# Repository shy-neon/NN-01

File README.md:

# NN-01
IR bridge based on attiny-85
</br>
</br>

</br>

## Description 
Imagine having different IR devices (e.g. a TV and an Home theatre hoked to it) each of them controlled by its own remote. This device allows you to control both of them with the same remote.
It can be field programmed (according to the flow diagram below) to emit a specific IR commad whenever a source IR command is recived, this can be useful to automate some scenarios (like turnig on the home theatre whenever the tv is turned on or controlling the volume from the TV remote).
This is expecially usefull when a generic universal remote cannot be used (modern smart TVs come with remotes which have oddly specific buttons for menus and so on...)

</br>
Repo provides the firmware (compatible with attiny 84, to be compiled with attinyCore), schematic and PCB layouts
</br>

### Partlist
1x 100uF - 16v electrolitic capacitor <a>> </br>
2x 0.1uF - ceramic capacitor </br>
1x GTC usb-c recepticle  <a href="https://www.digikey.it/it/products/detail/gct/USB4085-GF-A/9859662">available here </a> </br>
1x Atmel attiny 84 <a href="https://www.digikey.it/it/products/detail/microchip-technology/ATTINY85-20PU/735469">available here </a> </br> 
1x 1838 ir receiver </br>
1x 940/850 nm ir LED (at least 60°) <a href="https://www.digikey.it/it/products/detail/vishay-semiconductor-opto-division/TSAL7600/1681341">available here </a> </br>
1x red or visible LED  </br>
1x 330 ohm Resistor   </br>
1x 10k ohm Resistor   </br>
1x 220 ohm Resistor   </br>

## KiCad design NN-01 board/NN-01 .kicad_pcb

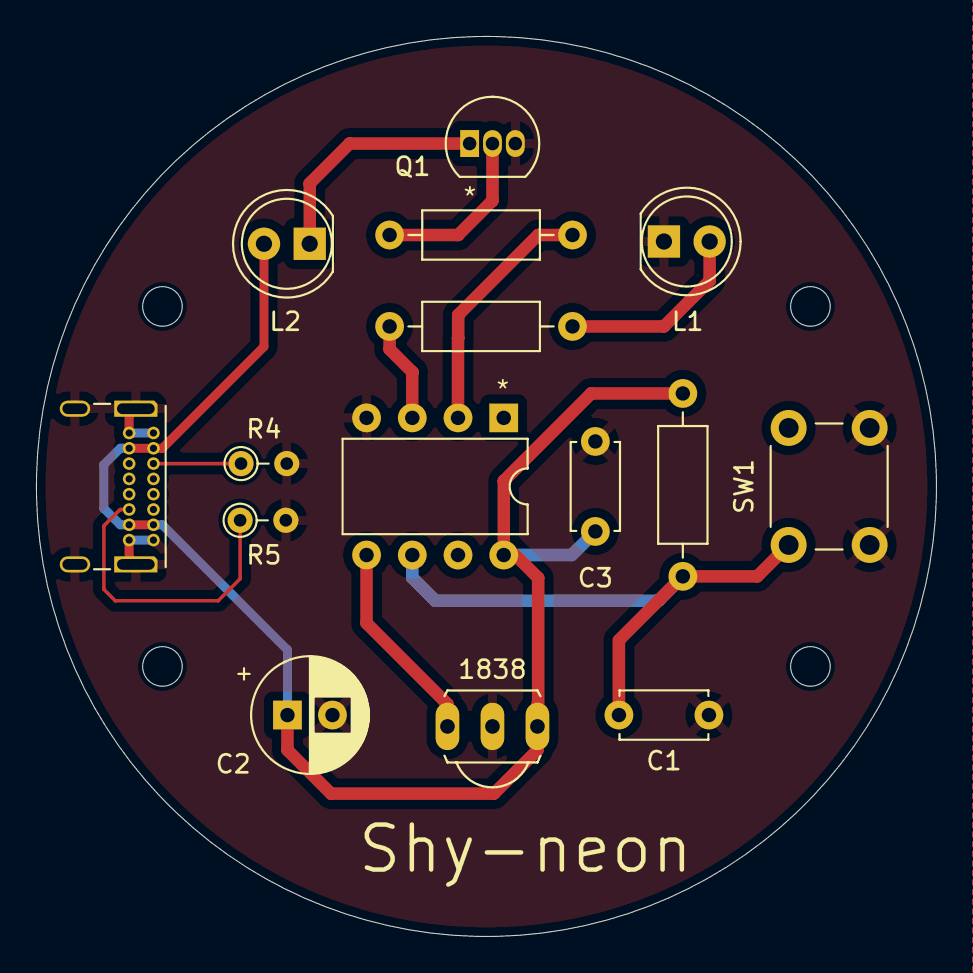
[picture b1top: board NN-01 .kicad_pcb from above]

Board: 2 copper layers, 50.0 x 50.0 mm, 15 parts (0 on the bottom side), 11 nets.

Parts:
C1: 0.1u; C_Disc_D4.7mm_W2.5mm_P5.00mm
C2: C; CP_Radial_D6.3mm_P2.50mm
C3: C; C_Disc_D4.7mm_W2.5mm_P5.00mm
D1, D2: LED; LED_D5.0mm
J2: USB4085-GF-A_REVB; USB_C_Receptacle_GCT_USB4085
Q1: BC337; TO-92_Inline
R1: 220; R_Axial_DIN0207_L6.3mm_D2.5mm_P10.16mm_Horizontal
R2: 10k; R_Axial_DIN0207_L6.3mm_D2.5mm_P10.16mm_Horizontal
R3: 330; R_Axial_DIN0207_L6.3mm_D2.5mm_P10.16mm_Horizontal
R4, R5: R; R_Axial_DIN0204_L3.6mm_D1.6mm_P2.54mm_Vertical
SW1: SW_Push_Dual_x2; SW_PUSH_6mm_H4.3mm
U1: ATtiny85-20P; DIP-8_W7.62mm
U2: TSOP1838; TSOP18XX

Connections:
GND: C1.2, C2.2, C3.2, D2.1 (K), J2.A1 (GND), J2.A12 (GND__1), J2.B1 (GND__2), J2.B12 (GND__3), J2.S1 (SHELL), Q1.3 (E), R4.2, R5.2, SW1.2 (D), U1.4 (GND), U2.GND
unnamed: D1.1 (K), Q1.1 (C)
unnamed: D2.2 (A), R3.2
unnamed: J2.A5 (CC1), R4.1
unnamed: J2.B5 (CC2), R5.1
unnamed: Q1.2 (B), R1.1
unnamed: C1.1, R2.1, SW1.1 (C), U1.6 (PB1)
unnamed: U1.5 (AREF/PB0), U2.OUT
unnamed: R1.2, U1.2 (XTAL1/PB3)
unnamed: R3.1, U1.3 (XTAL2/PB4)
VCC: C2.1, C3.1, D1.2 (A), J2.A4 (VBUS), J2.A9 (VBUS__1), J2.B4 (VBUS__2), J2.B9 (VBUS__3), R2.2, U1.8 (VCC), U2.VCC (V+)

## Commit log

2024-05-03 board
2024-05-03 program
2024-05-03 first
